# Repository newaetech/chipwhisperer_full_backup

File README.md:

# ChipWhisperer

 |  | 

## Important Links

[Hardware Docs](https://rtfm.newae.com) | [Software Docs](https://chipwhisperer.readthedocs.io) | [Tutorials](https://github.com/newaetech/chipwhisperer-jupyter/tree/main) | [Forum](http://forum.newae.com) | [Store](https://store.newae.com) | [NewAE](http://newae.com)

## ChipWhisperer 6.0: Repo Changes and Cleanup

ChipWhisperer 6.0 is bringing many changes to the ChipWhisperer repository. The biggest one is a cleanup of the git history on both this repo and
chipwhisperer-jupyter, as well as moving some files out of these repositories. We've done our best to make everything most users will want
on this repo, as well as to backup everything else to other repos.

For more information, please check out our [writeup on this update](https://docs.google.com/document/d/1sAhfBboymKDQyOE_BurCmwsh7hb_Qiw8SW3kCu9ZGrg/edit?usp=sharing).

## What is ChipWhisperer?

ChipWhisperer is an open source toolchain dedicated to hardware security research. This toolchain consists of several layers of open source components:
* __Hardware__: The ChipWhisperer uses a _capture_ board and a _target_ board. Schematics and PCB layouts for the ChipWhisperer-Lite capture board and a number of target boards are freely available.
* __Firmware__: Three separate pieces of firmware are used on the ChipWhisperer hardware. The capture board has a USB controller (in C) and an FPGA for high-speed captures (in Verilog) with open-source firmware. Also, the target device has its own firmware; this repository includes many firmware examples for different targets.
* __Software__: The ChipWhisperer software includes a Python API for talking to ChipWhisperer hardware (ChipWhisperer Capture) and a Python API 
for processing power traces from ChipWhisperer hardware (ChipWhisperer Analyzer). You can find documentation for our Python API at
chipwhisperer.readthedocs.io

## Getting Started
First time using ChipWhisperer? Check out these links:
* [Getting started](https://chipwhisperer.readthedocs.io/en/latest/getting-started.html)
* [Installing ChipWhisperer](https://chipwhisperer.readthedocs.io/en/latest/index.html#install) if you're trying to set up this software package
* [Hardware Docs](https://rtfm.newae.com) for hardware information. Also has helpful comparison between different NewAE products.

## GIT Source
Note all development occurs on the [develop](https://github.com/newaetech/chipwhisperer/tree/develop) branch. If you are looking for bleeding edge it's NOT on master - we push each release (and possibly any critical changes) to master. This means that "master" always gives you the latest known-working branch, but there may be new features on the "develop" branch.

## Help!
Stuck? If you need a hand, there are a few places you can ask for help:
* The [NewAE Forum](https://forum.newae.com/) is full of helpful people that can point you in the right direction
* If you find a bug, let us know through the [issue tracker](https://github.com/newaetech/chipwhisperer/issues)

---

ChipWhisperer is a trademark of NewAE Technology Inc., registered in the US, Europe, and China.

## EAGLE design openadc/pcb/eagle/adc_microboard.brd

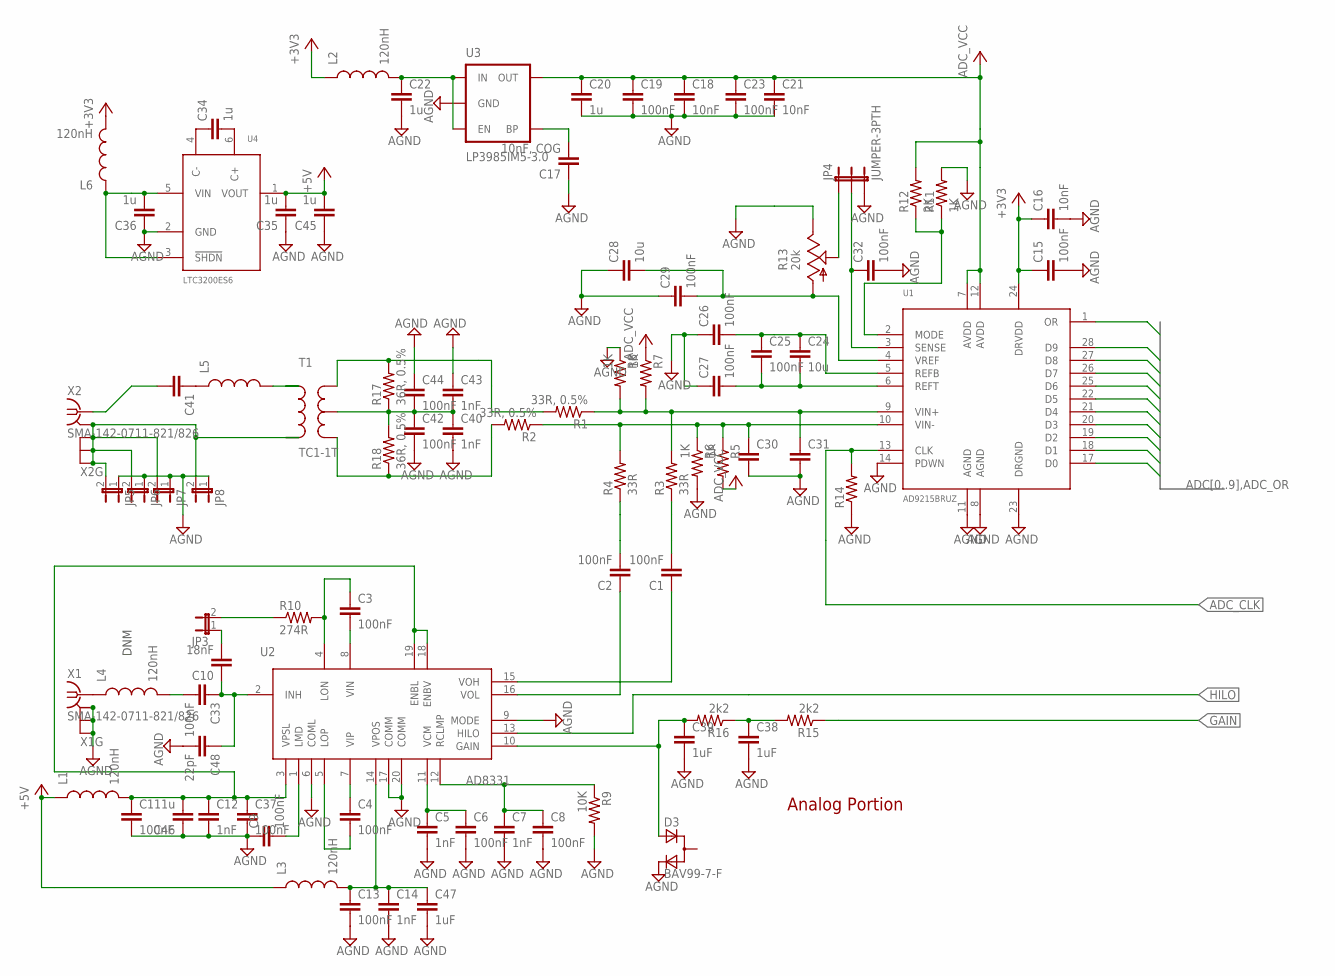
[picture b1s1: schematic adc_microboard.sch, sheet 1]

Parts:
C1, C2, C33: 100nF; C0603K
C3, C4: 100nF; C0402
C5, C7, C12, C14, C40, C43: 1nF; C0402; PART# C1005X7R1E102K; DIGIKEY# 445-4924-1-ND
C6, C8, C9, C11, C13, C15, C19, C23, C25, C26, C27, C29, C32, C37, C42, C44: 100nF; C0402; PART# GRM155R61A104KA01D; DIGIKEY# 490-1318-1-ND
C10: 18nF; C0603; DIGIKEY# 587-1099-1-ND
C16: 10nF; C0402; DIGIKEY# 490-1312-1-ND
C17: 10nF, COG; C0402; DIGIKEY# 445-2664-1-ND
C18, C21: 10nF; C0402; PART# GRM155R71E103KA01D; DIGIKEY# 490-1312-1-ND
C20, C22, C34, C35, C36, C45: 1u; C0603; PART# GRM188R61A105KA61D; DIGIKEY# 490-1543-1-ND
C24: 10u; C0603; DIGIKEY# C1608X5R0J106K
C28: 10u; C0603
C30, C31: C-EUC0402; C0402
C38, C39: 1uF; C0603
C41: C-EUC0603K; C0603K
C46: 1u; C0402; PART# GRM188R61A105KA61D; DIGIKEY# 490-1543-1-ND
C47: 1uF; C0402; PART# C1005X7R1E102K; DIGIKEY# 445-4924-1-ND
C48: 22pF; C0603; DIGIKEY# 587-1099-1-ND
D3: BAV99-7-F; SOT-23
JP3, JP5, JP6, JP7, JP8: JUMPER-2SMD-NC; SJ_2S
JP4: JUMPER-3PTH; 1X03
L1: 120nH; 0603; PART# MLF1608DR12M; DIGIKEY# 445-6234-1-ND
L2, L3, L4, L6: 120nH; 0603
L5: INDUCTOR0603; 0603
R1: 33R, 0.5%; R0603; DIGIKEY# RR08Q33DCT-ND
R2: 33R, 0.5%; R0603
R3, R4: 33R; R0603
R5: 1K; R0402; DIGIKEY# RHM1.00KCDCT-ND
R6, R7, R8, R11: 1K; R0402
R9: 10K; R0603
R10: 274R; R0603; DIGIKEY# RR08P274DCT-ND
R12: 2K; R0603
R13: 20k; 3361P; PART# 3361P-1-203GLF; DIGIKEY# 3361P-203GLFCT-ND
R14: R-US_R0603; R0603
R15, R16: 2k2; R0603
R17, R18: 36R, 0.5%; R0603; DIGIKEY# RR08Q36DCT-ND
T1: TC1-1T; AT224-1A
U1: AD9215BRUZ; TSSOP28; DIGIKEY# AD9215BRUZ-105-ND
U2: AD8331; QSOP20; PART# AD8331ARQZ; DIGIKEY# AD8331ARQZ-ND
U3: LP3985IM5-3.0; SOT23-5; DIGIKEY# LP3985IM5-3.0CT-ND
U4: LTC3200ES6; SOT23-6L; PART# LTC3200ES6-5#TRMPBF
X1, X2: SMA-142-0711-821/826; J502-ND-142-0711-821/826; DIGIKEY# CONSMA003.062-ND

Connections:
+3V3: C15.1, C16.1, L2.1, L6.2, U1.24 (DRVDD); also elsewhere on the board
+5V: C35.2, C45.2, L1.1, L3.1, U4.1 (VOUT)
ADC0: U1.17 (D0); also elsewhere on the board
ADC1: U1.18 (D1); also elsewhere on the board
ADC2: U1.19 (D2); also elsewhere on the board
ADC3: U1.20 (D3); also elsewhere on the board
ADC4: U1.21 (D4); also elsewhere on the board
ADC5: U1.22 (D5); also elsewhere on the board
ADC6: U1.25 (D6); also elsewhere on the board
ADC7: U1.26 (D7); also elsewhere on the board
ADC8: U1.27 (D8); also elsewhere on the board
ADC9: U1.28 (D9); also elsewhere on the board
ADC_CLK: R14.2, U1.13 (CLK); also elsewhere on the board
ADC_OR: U1.1 (OR); also elsewhere on the board
ADC_VCC: C18.1, C19.1, C20.1, C21.1, C23.1, R5.2, R7.1, R12.2, U1.7 (AVDD), U1.12 (AVDD), U3.5 (OUT)
AGND: C5.2, C6.2, C7.2, C8.2, C9.1, C11.2, C12.2, C13.2, C14.2, C15.2, C16.2, C17.1, C18.2, C19.2, C20.2, C21.2, C22.2, C23.2, C26.1, C27.1, C28.1, C29.1, C30.2, C31.2, C32.2, C35.1, C36.1, C37.2, C38.2, C39.2, C40.2, C42.2, C43.1, C44.1, C45.1, C46.1, C47.2, C48.2, D3.2 (C), JP4.3, JP5.1, JP6.1, JP7.1, JP8.1, R6.2, R8.1, R9.2, R11.2, R13.1 (E), R14.1, U1.8 (AGND), U1.11 (AGND), U1.14 (PDWN), U1.23 (DRGND), U2.6 (COML), U2.9 (MODE), U2.17 (COMM), U2.20 (COMM), U3.2 (GND), U4.2 (GND), X1.G@1 (GND), X1.G@2 (GND), X1.G@3 (GND), X1.G@4 (GND); also elsewhere on the board
GAIN: R15.1; also elsewhere on the board
HILO: U2.13 (HILO); also elsewhere on the board
unnamed: C31.1, R1.1, R3.2, R7.2, R8.2, U1.9 (VIN+)
unnamed: JP4.1, R13.2 (S)
unnamed: C1.2, R3.1
unnamed: C2.2, R4.1
unnamed: C4.2, U2.5 (LOP)
unnamed: C2.1, U2.16 (VOL)
unnamed: C1.1, U2.15 (VOH)
unnamed: C4.1, U2.7 (VIP)
unnamed: C3.2, U2.8 (VIN)
unnamed: C3.1, R10.2, U2.4 (LON)
unnamed: C5.1, C6.1, U2.11 (VCM)
unnamed: C7.1, C8.1, R9.1, U2.12 (RCLMP)
unnamed: C9.2, U2.1 (LMD)
unnamed: C10.2, JP3.1
unnamed: JP3.2, R10.1
unnamed: C10.1, C33.1, C48.1, U2.2 (INH)
unnamed: C17.2, U3.4 (BP)
unnamed: L4.1, X1.1
unnamed: C13.1, C14.1, C47.1, L3.2, U2.14 (VPOS)
unnamed: C22.1, L2.2, U3.1 (IN), U3.3 (EN)
unnamed: C24.1, C25.1, C26.2, U1.5 (REFB)
unnamed: C41.1, L5.1
unnamed: C24.2, C25.2, C27.2, U1.6 (REFT)
unnamed: C30.1, R2.1, R4.2, R5.1, R6.1, U1.10 (VIN-)
unnamed: C28.2, C29.2, R13.3 (A), U1.4 (VREF)
unnamed: C32.1, JP4.2, U1.3 (SENSE)
unnamed: R11.1, R12.1, U1.2 (MODE)
unnamed: L5.2, T1.6 (P1)
unnamed: JP5.2, JP6.2, JP7.2, JP8.2, T1.4 (P2), X2.G@1 (GND), X2.G@2 (GND), X2.G@3 (GND), X2.G@4 (GND)
unnamed: R1.2, R17.2, T1.1 (S1)
unnamed: C34.1, U4.4 (C-)
unnamed: C34.2, U4.6 (C+)
unnamed: C11.1, C12.1, C37.1, C46.2, L1.2, U2.3 (VPSL), U2.18 (ENBV), U2.19 (ENBL)
unnamed: C38.1, R15.2, R16.1
unnamed: C39.1, D3.3 (A), R16.2, U2.10 (GAIN)
unnamed: R2.2, R18.1, T1.3 (S2)
unnamed: C40.1, C42.1, C43.2, C44.2, R17.1, R18.2, T1.2 (ST)
unnamed: C41.2, X2.1
unnamed: C36.2, L6.1, U4.3 (!SHDN), U4.5 (VIN)
unnamed: C33.2, L4.2

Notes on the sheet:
Analog Portion
DNM

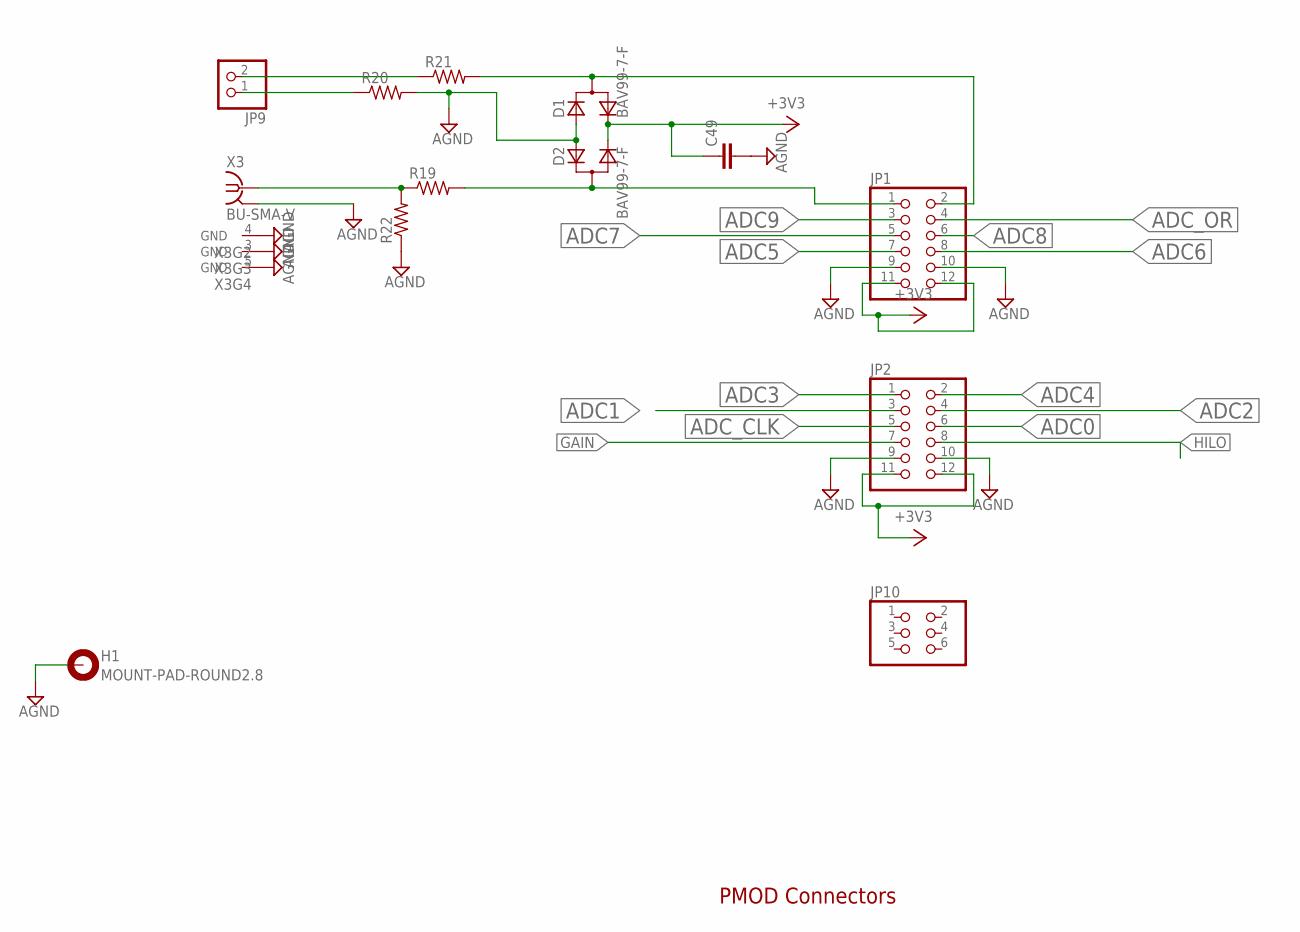
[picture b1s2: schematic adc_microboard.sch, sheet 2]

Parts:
C49: C-EUC0603; C0603
D1, D2: BAV99-7-F; SOT-23
H1: MOUNT-PAD-ROUND2.8; 2,8-PAD
JP1: PINHD-2X6; 2X06; DIGIKEY# 609-3373-ND
JP2: PINHD-2X6; 2X06
JP9: PINHD-1X2/90; 1X02/90; DIGIKEY# WM2711-ND
JP10: PINHD-2X3; 2X03
R19: R-US_R0805; R0805
R20, R21, R22: R-US_R0603; R0603
X3: BU-SMA-V

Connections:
+3V3: C49.1, D1.2 (C), D2.2 (C), JP1.11, JP1.12, JP2.11, JP2.12; also elsewhere on the board
ADC0: JP2.6; also elsewhere on the board
ADC1: JP2.3; also elsewhere on the board
ADC2: JP2.4; also elsewhere on the board
ADC3: JP2.1; also elsewhere on the board
ADC4: JP2.2; also elsewhere on the board
ADC5: JP1.7; also elsewhere on the board
ADC6: JP1.8; also elsewhere on the board
ADC7: JP1.5; also elsewhere on the board
ADC8: JP1.6; also elsewhere on the board
ADC9: JP1.3; also elsewhere on the board
ADC_CLK: JP2.5; also elsewhere on the board
ADC_OR: JP1.4; also elsewhere on the board
AGND: C49.2, D1.3 (A), D2.3 (A), H1.B2,8, JP1.9, JP1.10, JP2.9, JP2.10, R20.2, R22.1, X3.2 (GND), X3.3 (GND), X3.4 (GND), X3.5 (GND); also elsewhere on the board
GAIN: JP2.7; also elsewhere on the board
HILO: JP2.8; also elsewhere on the board
unnamed: D2.1 (CA), JP1.1, R19.2
unnamed: R19.1, R22.2, X3.1
unnamed: JP9.1, R20.1
unnamed: JP9.2, R21.1
unnamed: D1.1 (CA), JP1.2, R21.2

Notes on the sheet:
PMOD Connectors

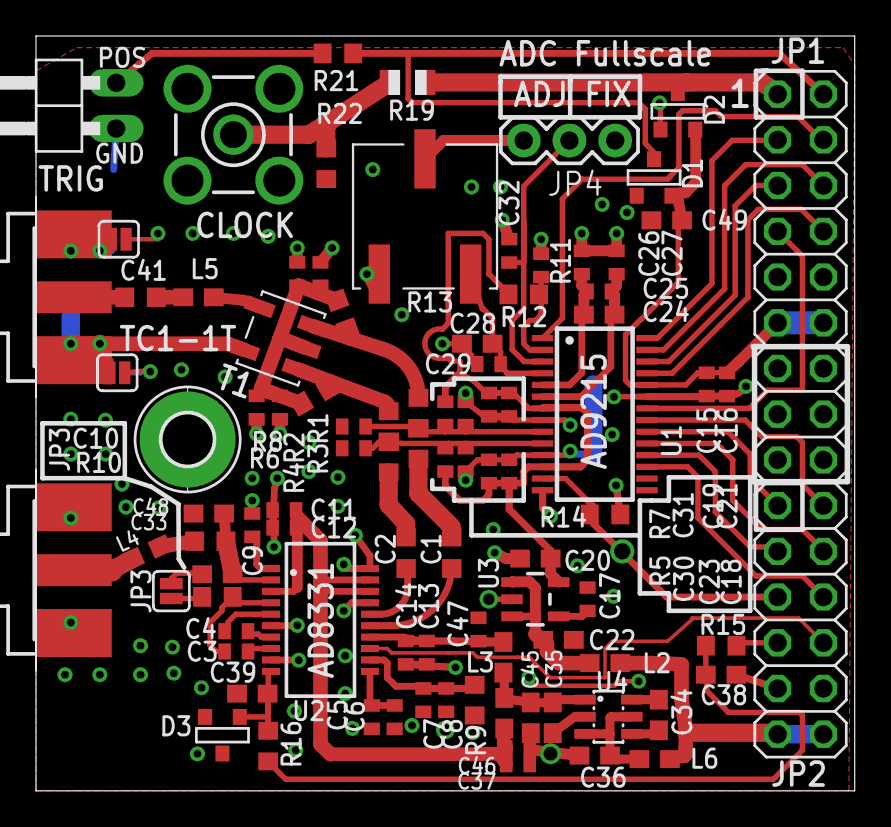
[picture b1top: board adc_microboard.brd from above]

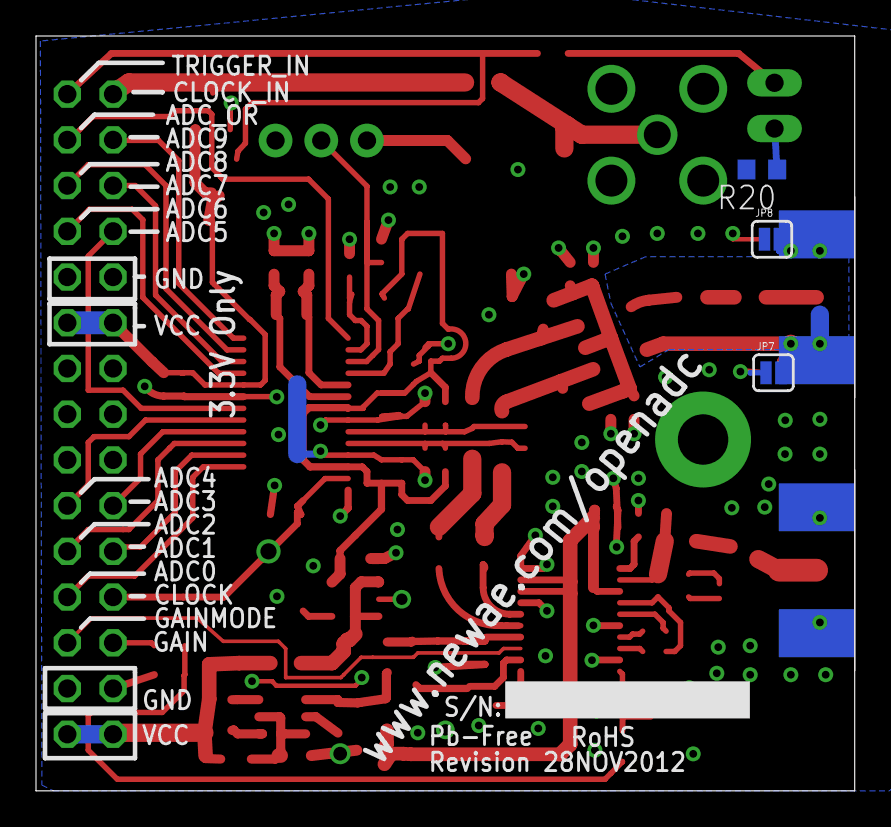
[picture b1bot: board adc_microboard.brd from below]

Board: 2 copper layers, 45.5 x 41.9 mm, 99 parts (3 on the bottom side), 63 nets.

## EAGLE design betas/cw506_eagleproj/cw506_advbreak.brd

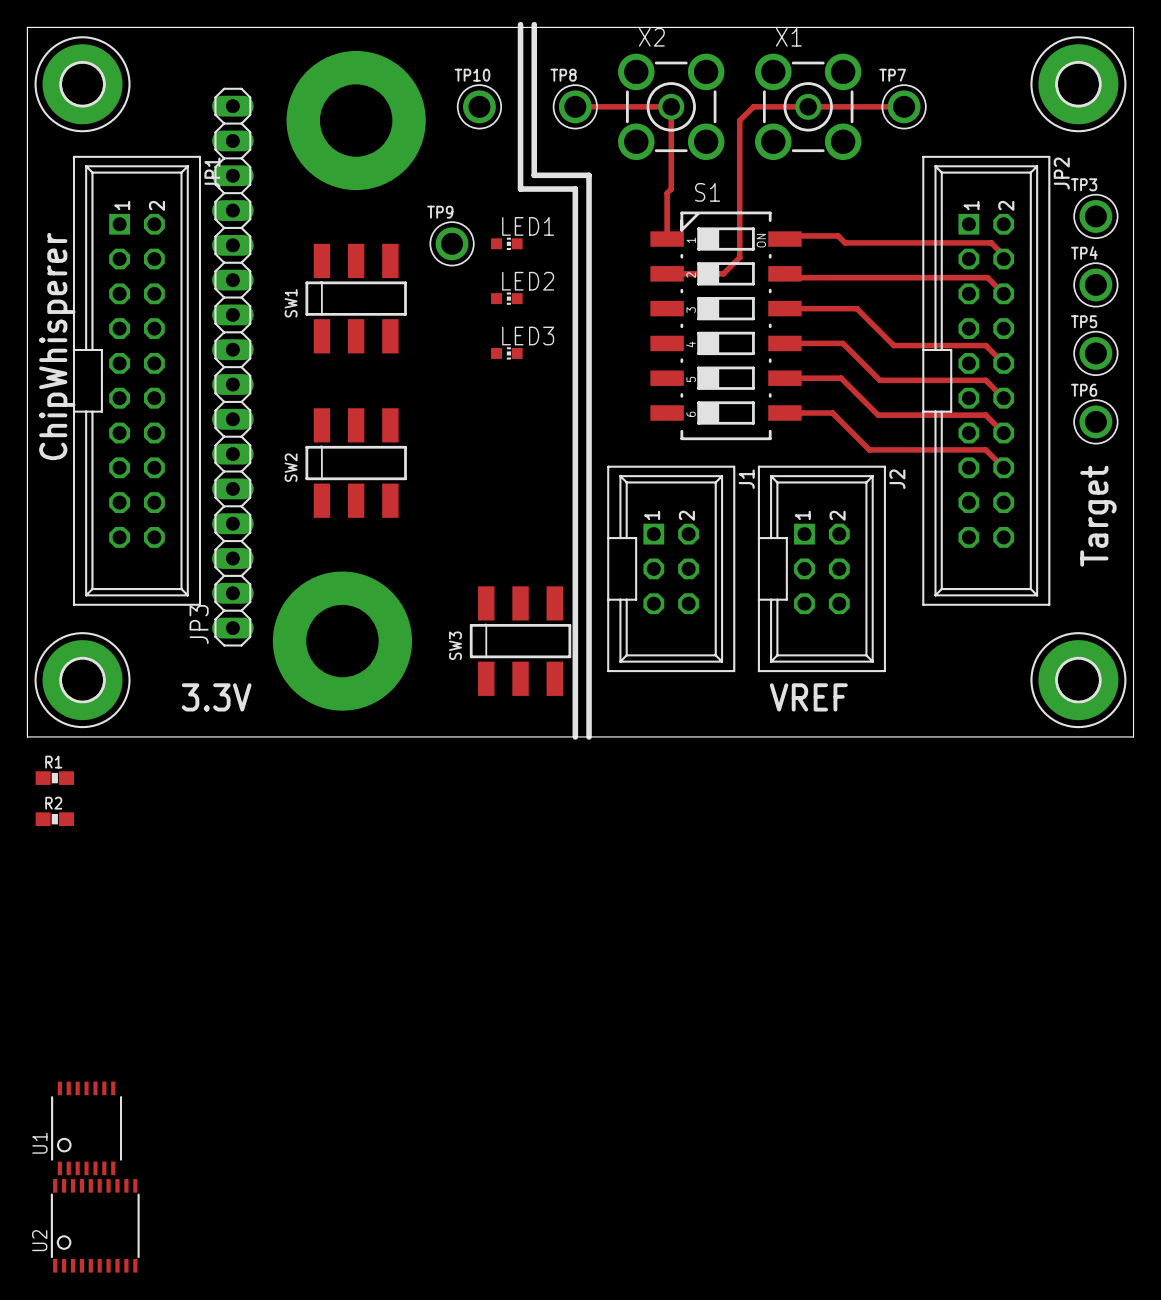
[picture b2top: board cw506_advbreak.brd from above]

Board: 2 copper layers, 80.8 x 51.8 mm, 32 parts (0 on the bottom side), 19 nets.

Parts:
H1, H2, H3, H4: MOUNT-PAD-ROUND3.0; 3,0-PAD
J1, J2: SHROUD_2X3; PINSHRD_PTH_2X03
JP1, JP2: CWTIO-20PIN; PINSHRD_PTH_2X10
JP3: 1X16
LED1, LED2, LED3: CHIP-LED0603
R1, R2: 0603R
S1: 219-06; CTS-219-06
SW1, SW2, SW3: JS202011SCQN
TP1, TP2: KEYSTONE575-4
TP3, TP4, TP5, TP6, TP7, TP8, TP9, TP10: KEYSTONE_TPCOMPACT
U1: TSSOP14
U2: TSSOP20
X1, X2: BU-SMA-V

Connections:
+3V3: JP1.3, SW1.1, SW3.3, SW3.4
GND: JP2.2, JP2.17, JP2.19, SW1.5, TP2.1, X1.2, X1.3, X1.4, X1.5, X2.2, X2.3, X2.4, X2.5
unnamed: SW1.3, SW2.5
unnamed: LED1.C, SW1.6
unnamed: SW1.4, SW2.2
unnamed: JP2.8, SW2.4
unnamed: LED3.C, SW2.3
unnamed: LED2.C, SW2.1
unnamed: SW2.6, SW3.1, SW3.6, TP1.1
unnamed: JP2.18, SW3.2, SW3.5
unnamed: S1.2, TP7.1, X1.1
unnamed: S1.1, TP8.1, X2.1
unnamed: R1.2, U1.2
THS1: JP2.4, S1.12
THS2: JP2.6, S1.11
TTIO1: JP2.10, S1.10
TTIO2: JP2.12, S1.9
TTIO3: JP2.14, S1.8
TTIO4: JP2.16, S1.7

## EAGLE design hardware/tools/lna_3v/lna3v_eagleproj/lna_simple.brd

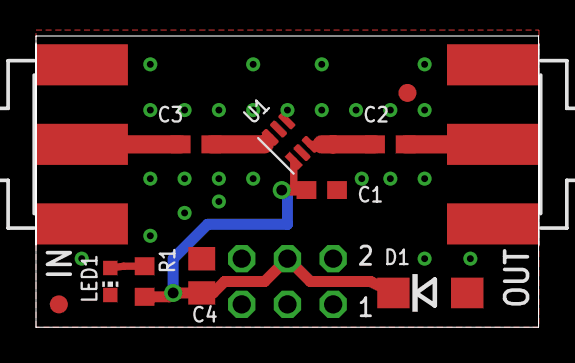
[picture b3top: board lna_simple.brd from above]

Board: 2 copper layers, 27.9 x 16.2 mm, 13 parts (1 on the bottom side), 7 nets.

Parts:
C1: 22nF; C0603
C2, C3: 100nF; C0603
C4: 4u7; C0805
D1: DO214AC
JP1: 2X03
LED1: CHIP-LED0603
R1: 330R; R0603
U1: BGA2801; SOTT323-6
U$1, U$2: FIDUCIAL; FIDUCIAL_1MM
X1, X2: SMA-142-0701-801/806; J502-ND-142-0701-801/806

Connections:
AGND: C1.2, C4.2, D1.A, JP1.6, LED1.C, U1.2, U1.4, U1.5, X1.G@1, X1.G@2, X1.G@3, X1.G@4, X2.G@1, X2.G@2, X2.G@3, X2.G@4
AVCC: C1.1, C4.1, D1.C, JP1.4, R1.2, U1.1
unnamed: C3.2, U1.6
unnamed: C2.1, U1.3
unnamed: C2.2, X2.1
unnamed: C3.1, X1.1
unnamed: LED1.A, R1.1

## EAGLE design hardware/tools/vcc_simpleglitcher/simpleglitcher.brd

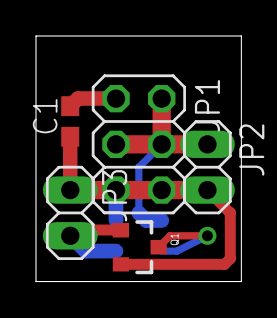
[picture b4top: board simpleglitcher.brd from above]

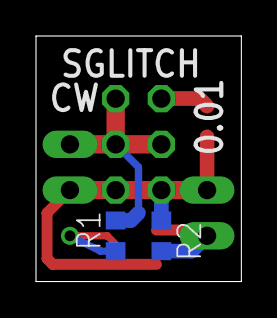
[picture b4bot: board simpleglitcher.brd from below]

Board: 2 copper layers, 11.4 x 13.6 mm, 7 parts (2 on the bottom side), 5 nets.

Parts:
C1: C0603
JP1: 2X03
JP2, JP3: 1X02
Q1: FDV301N; SOT23-3
R1: 0R; R0603
R2: 10k; R0603

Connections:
DGND: C1.1, JP1.5, JP1.6, JP2.2, JP3.1, Q1.2, R2.1
unnamed: JP1.2, JP1.3, JP1.4, JP2.1, R1.2
unnamed: Q1.3, R1.1
unnamed: C1.2, JP1.1
unnamed: JP3.2, Q1.1, R2.2

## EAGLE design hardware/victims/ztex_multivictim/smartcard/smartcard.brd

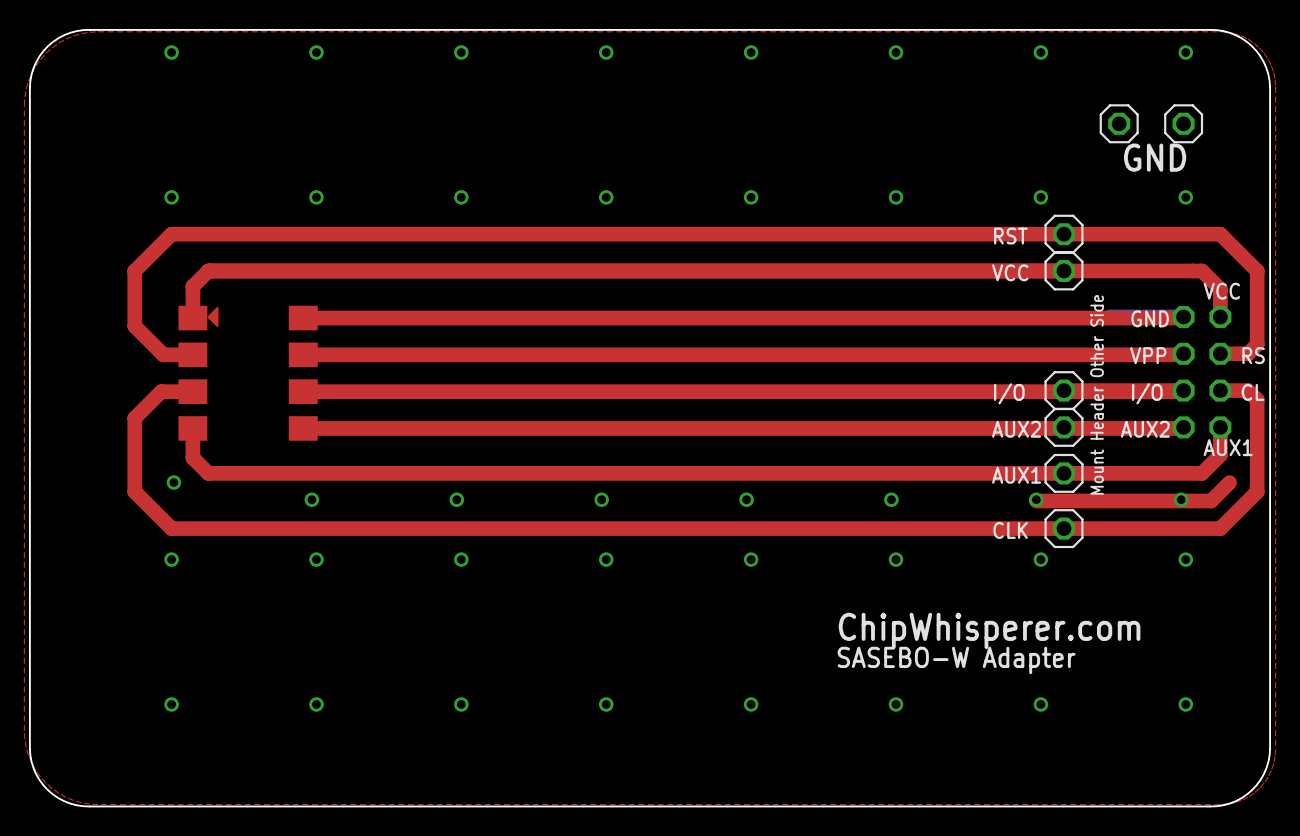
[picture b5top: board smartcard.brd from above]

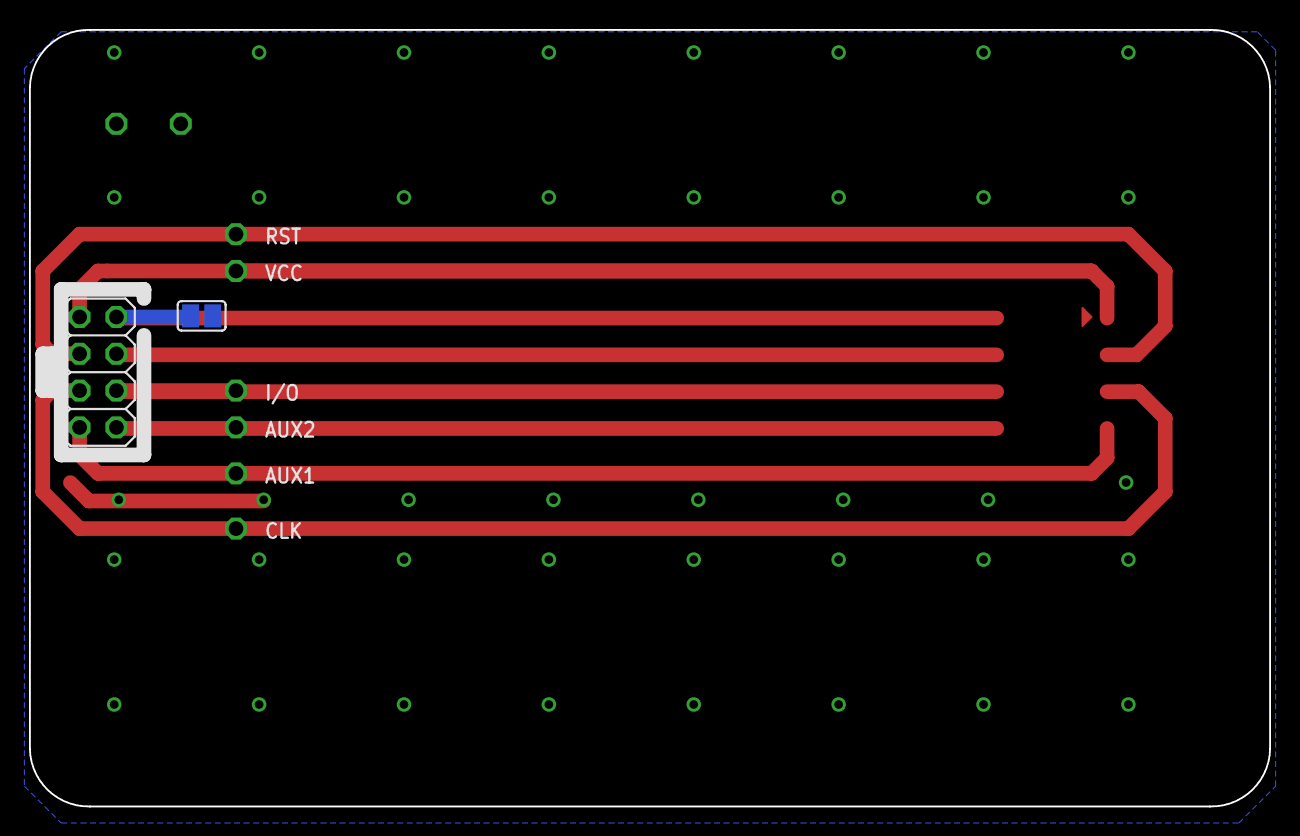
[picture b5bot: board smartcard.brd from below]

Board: 2 copper layers, 85.6 x 53.6 mm, 11 parts (2 on the bottom side), 9 nets.

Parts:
E$1: ISO7816
E$2: 2X04
E$3: SJ-NC
E$4, E$5, E$6, E$7, E$8, E$9, E$10, E$11: 1X01

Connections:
GND: E$3.2, E$4.1, E$6.1
S$1: E$1.P$1, E$2.8, E$8.1
S$2: E$1.P$5, E$2.7
S$3: E$1.P$6, E$2.5
S$4: E$1.P$7, E$2.3, E$5.1
S$5: E$1.P$8, E$2.1
S$6: E$1.P$2, E$2.6, E$9.1
S$8: E$1.P$3, E$2.4
S$9: E$1.P$4, E$2.2

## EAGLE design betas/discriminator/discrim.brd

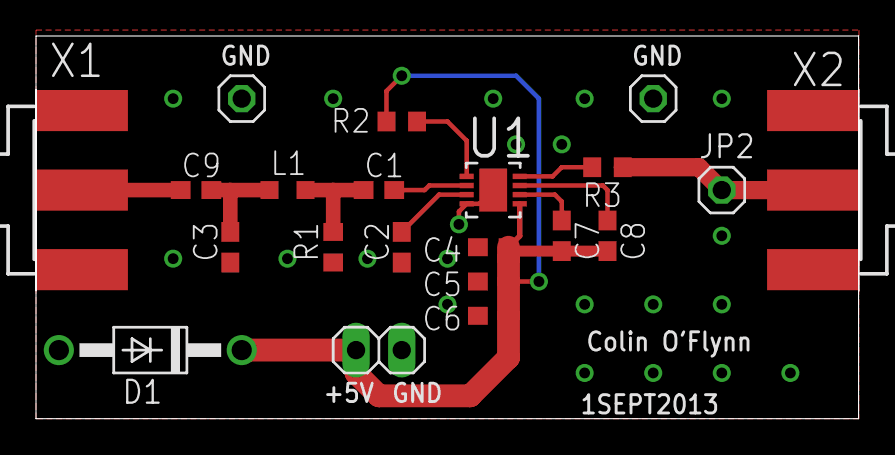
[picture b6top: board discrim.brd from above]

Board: 2 copper layers, 45.7 x 21.3 mm, 21 parts (0 on the bottom side), 12 nets.

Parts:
C1, C2, C3, C4, C5, C6, C7, C8, C9: C0603
D1: 1N4004; DO41-10
JP1: 1X02
JP2, JP3, JP4: 1X01
L1: L2012C
R1, R2, R3: R0603
U1: LT5538IDDPBF; DFN300X300X80-9N
X1, X2: SMA-142-0701-801/806; J502-ND-142-0701-801/806

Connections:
+5V: C4.1, C5.1, C6.1, C7.2, C8.2, D1.C, JP1.2, R2.2, U1.5
GND: C2.1, C3.1, C4.2, C5.2, C6.2, D1.A, JP1.1, JP3.1, JP4.1, R1.1, U1.4, U1.9, X1.G@1, X1.G@2, X1.G@3, X1.G@4, X2.G@1, X2.G@2, X2.G@3, X2.G@4
unnamed: C2.2, U1.3
unnamed: C1.2, U1.2
unnamed: C1.1, L1.2, R1.2
unnamed: C3.2, C9.2, L1.1
unnamed: C7.1, U1.6
unnamed: C8.1, U1.7
unnamed: C9.1, X1.1
unnamed: R3.2, U1.8
unnamed: R2.1, U1.1
unnamed: JP2.1, R3.1, X2.1

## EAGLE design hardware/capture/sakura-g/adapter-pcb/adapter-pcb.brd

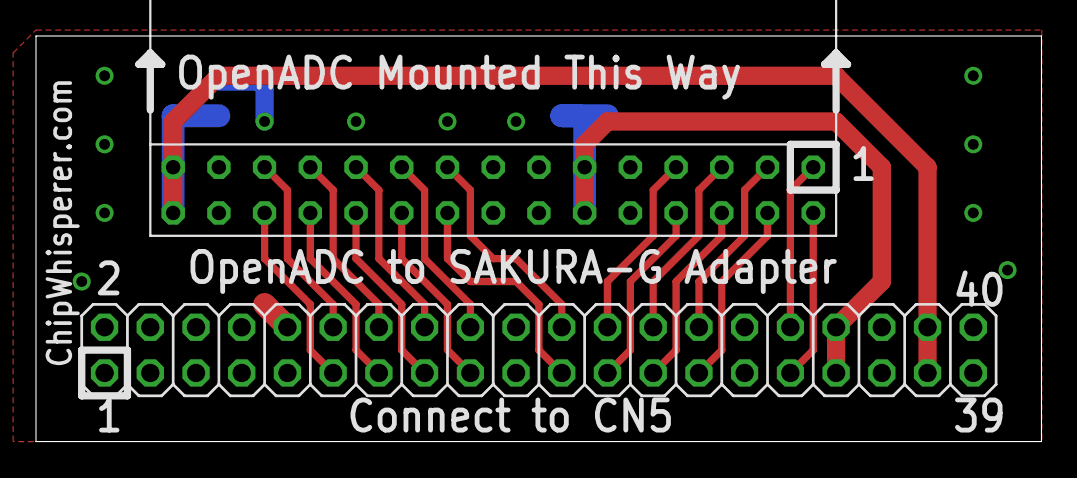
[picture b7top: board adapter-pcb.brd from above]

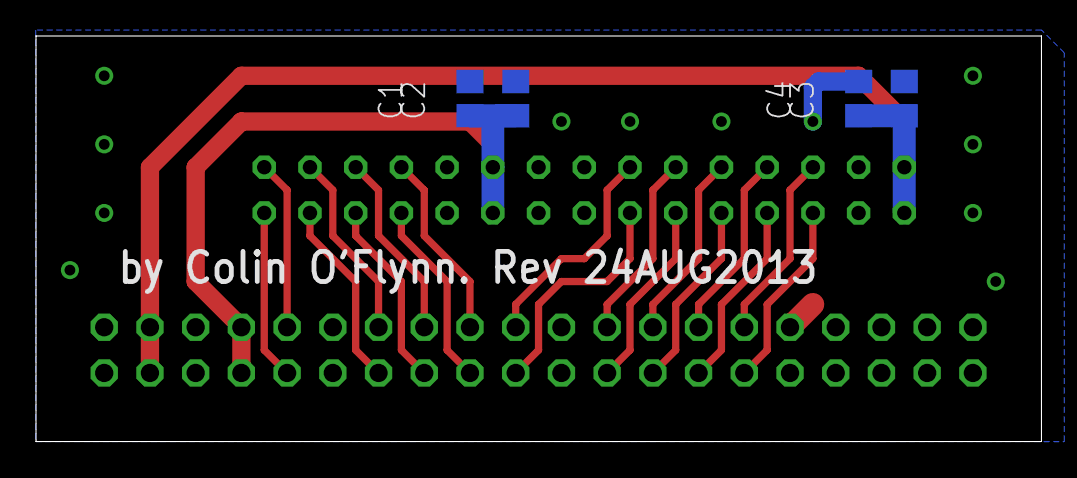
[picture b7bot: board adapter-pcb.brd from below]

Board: 2 copper layers, 55.9 x 22.5 mm, 6 parts (4 on the bottom side), 21 nets.

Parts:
C1, C2, C3, C4: C0805
JP1: 2X20
U$1: OPENADC; OPENADCREV1

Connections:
+3V3: C3.1, C4.1, JP1.37, JP1.38, U$1.29, U$1.30
ADC0: JP1.13, U$1.24
ADC1: JP1.16, U$1.21
ADC2: JP1.15, U$1.22
ADC3: JP1.18, U$1.19
ADC4: JP1.17, U$1.20
ADC5: JP1.24, U$1.7
ADC6: JP1.23, U$1.8
ADC7: JP1.26, U$1.5
ADC8: JP1.25, U$1.6
ADC9: JP1.28, U$1.3
ADCOR: JP1.27, U$1.4
CLKADC: JP1.14, U$1.23
GAIN: JP1.12, U$1.25
GND: C1.2, C2.2, C3.2, C4.2, JP1.9, JP1.10, JP1.19, JP1.20, JP1.29, JP1.30, JP1.35, JP1.36, U$1.9, U$1.10, U$1.27, U$1.28
HILO: JP1.11, U$1.26
unnamed: JP1.32, U$1.1
unnamed: JP1.31, U$1.2
unnamed: JP1.21, U$1.18
unnamed: JP1.22, U$1.17
VCCIO: C1.1, C2.1, JP1.33, JP1.34, U$1.11, U$1.12

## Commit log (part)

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2023-05-08 try without requirements?
2023-05-08 change requirements.txt for rtd
2023-05-08 reduce threshold on sam4s multi sad test
2023-05-09 update jupyter
2023-05-11 increase delay on sam4s reset
2023-05-11 Add warning if serial pins incorrect for F3/SAM4S
2023-05-15 Make scope.default_setup() show what it changed.
2023-05-17 Husky XADC: add user reset, enable/disable alarms
2023-05-18 Jupyter: update Husky notebooks
2023-05-24 Add pipelined AES FPGA target.
2023-05-24 Add packaged FPGA target bitfiles.
2023-05-24 remove pycryptodome dependency
2023-05-25 Jupyter (fix oops on last commit)
2023-05-29 Fix call to hex_decode (wrong argument order)
    hex_decode signature is:
    int hex_decode(int len, char* ascii_buf, uint8_t* data_buf);
2023-05-31 update linux docs to tell user to reset after udev rules
2023-06-05 Fixes for serial errors
2023-06-05 update juypter
2023-06-20 Husky PLL: towards fixing https://github.com/newaetech/chipwhisperer/issues/448
    More validation and testing required, especially since the CDCI6214
    datasheet is not super clear about the issue, but this fix seems to do
    the trick.
2023-06-22 Appease mypy.
2023-06-26 Jupyter
2023-06-26 Return requested # of samples when using as_int.
    On CW-Lite/Pro, additional samples could be returned.
2023-07-10 CW340 fpga read/write fixes
2023-07-11 Add documentation for CW312T_XC7A35T programmer
2023-07-12 switch PLL outputs on CW340
2023-07-12 CW340: add XADC
2023-07-13 fix target docstrings
2023-07-13 appease mypy
2023-07-27 Husky triggering updates.
    1. Allow SAD to generate triggers when not armed (i.e. after the ADC
    capture is done).
    2. Retrieve timestamped trigger times (when using multiple triggers).
2023-07-27 Arm RSA WIP changes
2023-07-30 Add error message with prog_type is None
    Inform the user that no programmer has been selected and the target will
    not be programmed
2023-08-15 FPGA targets: move ss2 wrapper to fpga-common.
2023-08-15 Add SS2-style iCE40 AES FPGA target.
    This allows iCE40 to be treated as a pseudo-CW305 target (see CW305 AES
    notebook).
2023-08-15 add timeout to tx, doc PDIC, make box_zoom default in plot
2023-08-17 Allow CW310/340 to use all CW305 properties.
2023-08-17 Add ext_offset[x] = y support for multiglitch
2023-08-22 disable code loop opt on sam4s
2023-08-26 Refactored vcc glitch mosfet control; Refactored default and glitch setup/disable API; Added message utilities; Added optimized data copy; Added API utilities and tests
2023-08-28 Husky USERIO: print info about each pin.
2023-08-29 Husky trigger sequencer: add validity checks.
    Prevent illegal combination of trigger modules and warn if setting
    trigger windows that can never fire.
2023-08-30 Tweaks towards supporting > 2 sequence triggers.
2023-09-01 Husky trig seq: option to make SAD always active.
2023-09-01 MultiGlitch typo
2023-09-05 update virtual box instructions for potential USB issue
2023-09-05 Add target FW for trace-less uecc attack notebook.
2023-09-10 Optimized GlitchController iterator and added utilites; Added glitch looper API; Added Simple Serial glitch looper test script
2023-09-12 add make command to custom firmware
2023-09-15 make clean no longer requires platform, update custom-firmware docs
2023-09-15 Fix lite build
2023-09-20 Add usart capability to CW340
2023-09-21 Add fw_path option to scope.upgrade_firmware()
    Also checks to make sure file exists
2023-09-26 Husky: make default_setup() reset segments to 1
2023-10-01 Refactored GPIO API
2023-10-05 Fix removal of inaccessible devices
    This PR fixes the incorrect removal of inaccessible devices in the get_possible_devices function.
2023-10-09 [naeusb] Remove claimInterface
    Remove `self.handle.claimInterface(0)` to enable connection for CW305.
2023-10-10 Add getCWType to cw340
2023-10-16 Husky: fix https://github.com/newaetech/chipwhisperer-husky-fpga/issues/17 and add more testing around it.
2023-10-24 More Husky 64-bit clock ints, add was_fpga_prog_on_con()
2023-10-27 add nbstripout to install instructions
2023-10-31 Remove old FPGA target material.
2023-10-31 Target FPGA: remove duplicate source files.
2023-11-01 Update target FPGA classes as per recent changes.
    Also adding small niceties like ability to print the target object.
2023-11-02 Add RTFM links to FPGA targets README.
2023-11-03 typo
2023-11-06 fix docstring
2023-11-19 FPGA register updates.
    Functionally equivalent. FPGA register address space was getting tight
    and so some were combined or eliminated. FPGA-side changes are:
    https://github.com/newaetech/chipwhisperer-husky-fpga/commit/7e0bec0497cc4ab0be0edc18e0264e9167e5a83e
2023-11-23 FPGA targets: fix AES defines file.
    Name/location were wrong, due to recent target FPGA organizational
    changes.
2024-01-02 Bump tj-actions/changed-files in /.github/workflows
    Bumps [tj-actions/changed-files](https://github.com/tj-actions/changed-files) from 29.0.1 to 41.0.0.
    - [Release notes](https://github.com/tj-actions/changed-files/releases)
    - [Changelog](https://github.com/tj-actions/changed-files/blob/main/HISTORY.md)
    - [Commits](https://github.com/tj-actions/changed-files/compare/v29.0.1...v41.0.0)
    ---
    updated-dependencies:
2024-01-16 CW305: add option to not program ss2 targets.
2024-03-20 Test push
2024-03-20 Fix tracewhisperer docs
2024-03-30 make BAUD_RATE definable
2024-03-30 remove FOSC defines, make everything based on F_CPU
2024-03-30 change default baud_rate
2024-03-30 fixes
2024-04-11 Husky SAD updates WIP.
2024-04-15 Add xonxoff support
2024-04-15 WIP nRST high-z fix (issue 481)
2024-04-17 Fix test_s6.py test script.
    Renamed from test_s6_glitch.py, because it now does more than glitch
    testing: it also checks the CW generated clock.
2024-04-17 Remove double glitch warning.
    Well tested by tests/test_s6.py; confident that double glitches are no
    longer a thing.
2024-05-30 Add scope.glitch.mmcm_locked property Lite/Pro.
2024-06-18 glitch controller plot fixes, allow saving and loading of results
2024-06-27 fix? multiple definition in makefile
2024-07-20 More Husky SAD updates, very much WIP.
2024-08-12 update hal platform message
2024-08-13 move mcu firmware to firmware/mcu
2024-08-14 remove hardware/capture and common
2024-08-14 remove misc targets
2024-08-14 remove final hardware files
2024-08-14 Husky SAD: add unblock for writing reference.
    With new implementations, this is needed after an unsuccessful capture.
2024-08-14 fix simpleserial doc path
2024-08-15 Husky: fix times reported by get_trigger_times()
    They were 2 cycles short.
2024-08-16 SAD explorer: clear capture_trace() output
2024-08-20 SAD model: small improvements (for demo).
2024-08-21 Husky SAD: allow reference update w/always_armed
2024-08-22 SAD explorer improvements.
    Add the trigger_sample property;
    do some sanity checking of the capture parameters before going ahead.
2024-08-22 SAD explorer improvements.
    - make enabled_samples functional
    - add extra_presamples feature
    - account for trigger_sample in calc_sad()
2024-08-23 SAD model: add enabled samples, advanced trigger.
2024-08-29 Husky: don't arm if XADC error disables trigger.
    XADC error shuts down MMCMs and SAD; the blinking red lights may not be
    enough (guilty as charged), so explicitely alert user that trying to
    capture is pointless.
2024-08-30 Husky SAD demo notebook.
2024-08-30 update jupyter (path updates)
2024-08-31 Update LICENSE.txt
    Default to apache2 (doesn't override anything else, some files are GPL still)
2024-09-20 Jupyter updates (bokeh 3.x).
2024-09-23 SAD explorer: workaround ipywidgets bug.
    Using Textarea() instead of Text() as per https://github.com/jupyter-widgets/ipywidgets/issues/3915
2024-09-25 Change to pyproject
2024-10-03 wip pyporoject
2024-10-15 Jupyter updates.
2024-10-22 Big update to PLL programming.
    Updates all PLL registers, in the prescribed order, whenever any of them
    needs to be updated. Towards fixing
    https://github.com/newaetech/chipwhisperer/issues/490.
    Functional (but not fully tested) for XIN case; not tested at all with
    external clock.
2024-10-25 Husky PLL cleanup.
2024-10-31 Husky clock: fixes for extclk case.
    - calculate PLL settings with the user-specified clock frequency instead
    of the measured clock frequency
    - similarly, scope.clock.pll.target_freq now reflects the user-specified
    frequency instead of the measured frequency
    - recover gracefully when clock setup fails
2024-10-31 Husky clocks: fix bypass mode (aka 'extclk_dir').
2024-11-04 Husky clocks cleanup.
2024-11-05 Rerun lint python when changing yml file
2024-11-05 Husky clocks: add PLL register dump function.
2024-11-07 Husky clocks: fix chX_iod_div width typo.
    Harmless, unless wanting to drive out a bypass clock.
2024-11-12 Replace python fw files with regular files
2024-11-14 Husky (ext)clocks: move ZDM set/clear update.
    Move it from clkgen_src to clkgen_freq, since the ability to use ZDM is
    frequency-dependent (can't use when input clock is above 100 MHz).
2024-11-15 Husky clocks: misc enhancements.
    - clarify ADC phase messaging
    - stop searching for PLL settings once error reaches 0
    - warn at > 250 MHz instead of > 200 MHz for Husky Plus
2024-11-15 Husky clocks: tweak PLL register updates.
    Don't update registers that are R/O, reserved, or that we don't care
    about.
2024-11-17 Extract files from .py files
2024-11-21 Husky clocks: minor fixes.
    - clarify clock frequency limits and warn when they're exceeded
    - fix a bug which would turn ADC clock back on when it had been turned off
    - warn if the generated clock is significantly far off from the requested clock
2024-11-21 Fix mypy
2024-11-25 Husky clocks: move update_fpga_vco().
    Do it after cache is written out so that it doesn't use stale values.
    Otherwise some clock changes can fail.
2024-11-25 Cast get_last_trace() to int64
2024-11-25 Tweak test_husky.py for clock changes.
    Allow for ADC frequency to not be exactly what was requested; minimize
    repeats on test_pll because it's better covered in new test notebooks
    (see previous commit). Could eliminate test_pll() altogether.
2024-11-26 Revert back to numpy 1.26.4 for now
2024-11-26 Husky clocks: add adc_phase warning to docs.
2024-11-28 Add requirements.txt, only run test server on develop push
2024-12-03 Move lesser used firmware to submodule
2024-12-03 Finish moving over to new binary file sys
2024-12-03 Clone submodule in build_firmware.yml
2024-12-03 Add .a files to fw-extra
2024-12-08 Fix fwver nano
2024-12-18 update juptyer
2024-12-18 Don't use .dep file
2024-12-18 Run update_private when updating firmware
2025-01-09 Try fixing python install in actions
2025-01-09 Also fix? pub pypi
2025-01-16 Husky clock testing tweak.
    In part 2, don't test for phase monotonicity because doing it properly
    would actually be redundant.
2025-01-17 Change jupyter back to master for easier merging.
    (was previously on ches2024sad which I wasn't planning on merging)
2025-01-21 New Husky bitfiles (big SAD update).
2025-01-21 Jupyter update (Husky SAD/clock improvements).
2025-01-22 Handle user not having bokeh for sad_explorer
2025-01-22 Install types for mypy in lint_python
2025-01-22 Target FPGA fixes.
    Update where Verilog register definitions are read from.
2025-01-23 Update jupyter (cw305 notebooks).
2025-01-27 Husky testing: split test_husky.py in two.
    test_husky_prod.py for production testing;
    test_husky_dev.py for development testing.
2025-01-31 Fix docs for linux install: udev rules have beem moved to root folder
    50-newae.rules probably was in the hardware folder at some point in time, but now it is in the root folder of the git repository
    Fixes #512
2025-02-08 Fix docs for updating firmware: udev rules file has been moved to root folder
    The file of the udev rules has been moved to the root folder of the repository.
    See #512 #513
    Since the instructions involve multiple steps (copy file, create group, join group, restart), I think it is best to just reference the instructions from the install guide.

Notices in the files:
parts and their libraries:
SparkFun: Licensing: CC v3.0 Share-Alike You are welcome to use this library for commercial purposes.
